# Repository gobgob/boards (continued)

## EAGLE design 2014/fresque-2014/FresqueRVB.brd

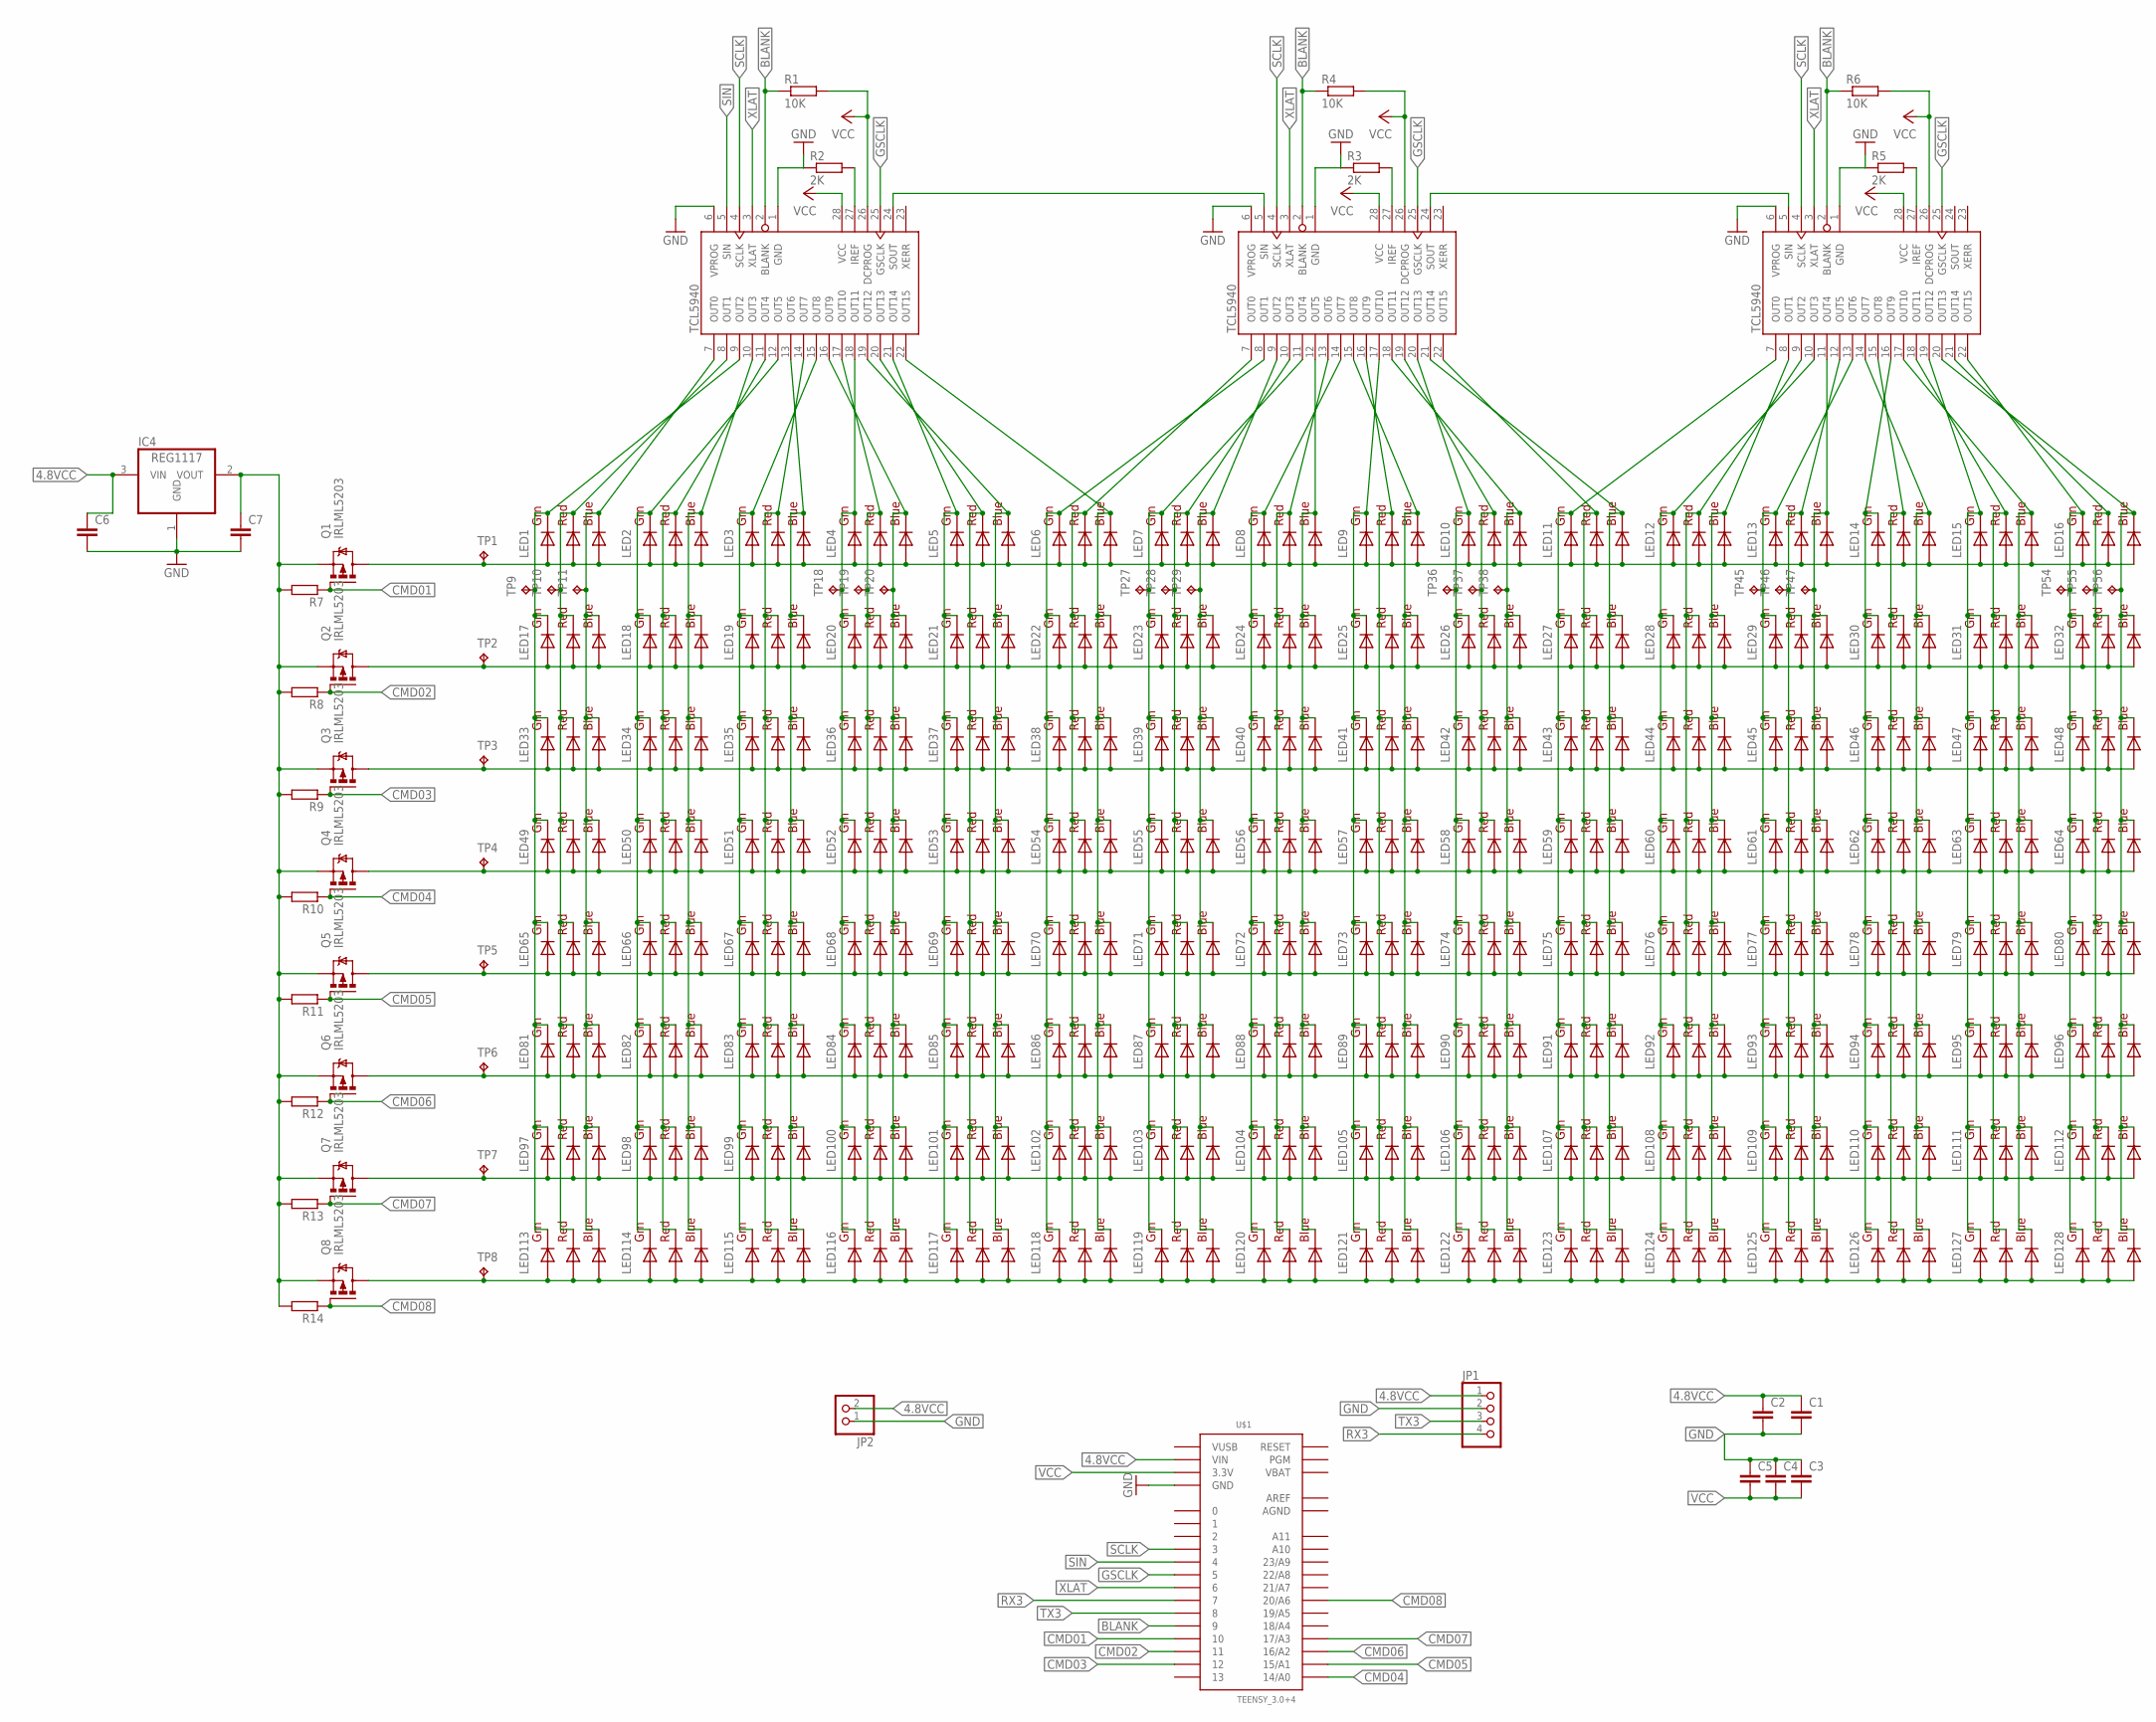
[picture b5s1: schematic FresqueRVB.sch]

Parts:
C1, C2, C3, C4, C5, C6, C7: C-EUC0603K; C0603K
IC1, IC2, IC3: TCL5940_TCL5940PWP; TCL5940_PWP
IC4: REG1117; SOT223
JP1: PINHD-1X4; 1X04
JP2: PINHD-1X2; 1X02
LED1, LED2, LED3, LED4, LED5, LED6, LED7, LED8, LED9, LED10, LED11, LED12, LED13, LED14, LED15, LED16, LED17, LED18, LED19, LED20, LED21, LED22, LED23, LED24, LED25, LED26, LED27, LED28, LED29, LED30, LED31, LED32, LED33, LED34, LED35, LED36, LED37, LED38, LED39, LED40, LED41, LED42, LED43, LED44, LED45, LED46, LED47, LED48, LED49, LED50, LED51, LED52, LED53, LED54, LED55, LED56, LED57, LED58, LED59, LED60, LED61, LED62, LED63, LED64, LED65, LED66, LED67, LED68, LED69, LED70, LED71, LED72, LED73, LED74, LED75, LED76, LED77, LED78, LED79, LED80, LED81, LED82, LED83, LED84, LED85, LED86, LED87, LED88, LED89, LED90, LED91, LED92, LED93, LED94, LED95, LED96, LED97, LED98, LED99, LED100, LED101, LED102, LED103, LED104, LED105, LED106, LED107, LED108, LED109, LED110, LED111, LED112, LED113, LED114, LED115, LED116, LED117, LED118, LED119, LED120, LED121, LED122, LED123, LED124, LED125, LED126, LED127, LED128: RGBLED5050
Q1, Q2, Q3, Q4, Q5, Q6, Q7, Q8: IRLML5203; MICRO3
R1, R4, R6: 10K; R0603
R2, R3, R5: 2K; R0603
R7, R8, R9, R10, R11, R12, R13, R14: R-EU_R0603; R0603
TP1, TP2, TP3, TP4, TP5, TP6, TP7, TP8, TP9, TP10, TP11, TP18, TP19, TP20, TP27, TP28, TP29, TP36, TP37, TP38, TP45, TP46, TP47, TP54, TP55, TP56: TPPAD1-13; P1-13
U$1: TEENSY_3.0+4

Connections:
4.8VCC: C1.1, C2.1, C6.1, IC4.3 (VIN), JP1.1, JP2.2, U$1.VBAT, U$1.VIN
AGND: U$1.AGND
AREF: U$1.AREF
BLANK: IC1.2 (BLANK), IC2.2 (BLANK), IC3.2 (BLANK), R1.1, R4.1, R6.1, U$1.9
CMD01: Q1.1 (G), R7.1, U$1.10
CMD02: Q2.1 (G), R8.1, U$1.11
CMD03: Q3.1 (G), R9.1, U$1.12
CMD04: Q4.1 (G), R10.1, U$1.14/A0
CMD05: Q5.1 (G), R11.1, U$1.15/A1
CMD06: Q6.1 (G), R12.1, U$1.16/A2
CMD07: Q7.1 (G), R13.1, U$1.17/A3
CMD08: Q8.1 (G), R14.1, U$1.20/A6
GND: C1.2, C2.2, C3.1, C4.1, C5.1, C6.2, C7.2, IC1.1 (GND), IC1.6 (VPROG), IC2.1 (GND), IC2.6 (VPROG), IC3.1 (GND), IC3.6 (VPROG), IC4.1 (GND), JP1.2, JP2.1, R2.1, R3.1, R5.1, U$1.GND, U$1.GND1 (GND)
GSCLK: IC1.25 (GSCLK), IC2.25 (GSCLK), IC3.25 (GSCLK), U$1.5
unnamed: IC2.27 (IREF), R3.2
unnamed: IC1.27 (IREF), R2.2
unnamed: IC3.27 (IREF), R5.2
unnamed: IC1.9 (OUT2), LED1.6 (GREEN_C), LED17.6 (GREEN_C), LED33.6 (GREEN_C), LED49.6 (GREEN_C), LED65.6 (GREEN_C), LED81.6 (GREEN_C), LED97.6 (GREEN_C), LED113.6 (GREEN_C), TP9.TP
unnamed: IC1.8 (OUT1), LED1.5 (RED_C), LED17.5 (RED_C), LED33.5 (RED_C), LED49.5 (RED_C), LED65.5 (RED_C), LED81.5 (RED_C), LED97.5 (RED_C), LED113.5 (RED_C), TP10.TP
unnamed: IC1.7 (OUT0), LED1.4 (BLUE_C), LED17.4 (BLUE_C), LED33.4 (BLUE_C), LED49.4 (BLUE_C), LED65.4 (BLUE_C), LED81.4 (BLUE_C), LED97.4 (BLUE_C), LED113.4 (BLUE_C), TP11.TP
unnamed: IC1.12 (OUT5), LED2.6 (GREEN_C), LED18.6 (GREEN_C), LED34.6 (GREEN_C), LED50.6 (GREEN_C), LED66.6 (GREEN_C), LED82.6 (GREEN_C), LED98.6 (GREEN_C), LED114.6 (GREEN_C)
unnamed: IC1.11 (OUT4), LED2.5 (RED_C), LED18.5 (RED_C), LED34.5 (RED_C), LED50.5 (RED_C), LED66.5 (RED_C), LED82.5 (RED_C), LED98.5 (RED_C), LED114.5 (RED_C)
unnamed: IC1.10 (OUT3), LED2.4 (BLUE_C), LED18.4 (BLUE_C), LED34.4 (BLUE_C), LED50.4 (BLUE_C), LED66.4 (BLUE_C), LED82.4 (BLUE_C), LED98.4 (BLUE_C), LED114.4 (BLUE_C)
unnamed: IC1.15 (OUT8), LED3.6 (GREEN_C), LED19.6 (GREEN_C), LED35.6 (GREEN_C), LED51.6 (GREEN_C), LED67.6 (GREEN_C), LED83.6 (GREEN_C), LED99.6 (GREEN_C), LED115.6 (GREEN_C)
unnamed: IC1.14 (OUT7), LED3.5 (RED_C), LED19.5 (RED_C), LED35.5 (RED_C), LED51.5 (RED_C), LED67.5 (RED_C), LED83.5 (RED_C), LED99.5 (RED_C), LED115.5 (RED_C)
unnamed: IC1.13 (OUT6), LED3.4 (BLUE_C), LED19.4 (BLUE_C), LED35.4 (BLUE_C), LED51.4 (BLUE_C), LED67.4 (BLUE_C), LED83.4 (BLUE_C), LED99.4 (BLUE_C), LED115.4 (BLUE_C)
unnamed: IC1.18 (OUT11), LED4.6 (GREEN_C), LED20.6 (GREEN_C), LED36.6 (GREEN_C), LED52.6 (GREEN_C), LED68.6 (GREEN_C), LED84.6 (GREEN_C), LED100.6 (GREEN_C), LED116.6 (GREEN_C), TP18.TP
unnamed: IC1.17 (OUT10), LED4.5 (RED_C), LED20.5 (RED_C), LED36.5 (RED_C), LED52.5 (RED_C), LED68.5 (RED_C), LED84.5 (RED_C), LED100.5 (RED_C), LED116.5 (RED_C), TP19.TP
unnamed: IC1.16 (OUT9), LED4.4 (BLUE_C), LED20.4 (BLUE_C), LED36.4 (BLUE_C), LED52.4 (BLUE_C), LED68.4 (BLUE_C), LED84.4 (BLUE_C), LED100.4 (BLUE_C), LED116.4 (BLUE_C), TP20.TP
unnamed: IC1.21 (OUT14), LED5.6 (GREEN_C), LED21.6 (GREEN_C), LED37.6 (GREEN_C), LED53.6 (GREEN_C), LED69.6 (GREEN_C), LED85.6 (GREEN_C), LED101.6 (GREEN_C), LED117.6 (GREEN_C)
unnamed: IC1.20 (OUT13), LED5.5 (RED_C), LED21.5 (RED_C), LED37.5 (RED_C), LED53.5 (RED_C), LED69.5 (RED_C), LED85.5 (RED_C), LED101.5 (RED_C), LED117.5 (RED_C)
unnamed: IC1.19 (OUT12), LED5.4 (BLUE_C), LED21.4 (BLUE_C), LED37.4 (BLUE_C), LED53.4 (BLUE_C), LED69.4 (BLUE_C), LED85.4 (BLUE_C), LED101.4 (BLUE_C), LED117.4 (BLUE_C)
unnamed: IC2.8 (OUT1), LED6.6 (GREEN_C), LED22.6 (GREEN_C), LED38.6 (GREEN_C), LED54.6 (GREEN_C), LED70.6 (GREEN_C), LED86.6 (GREEN_C), LED102.6 (GREEN_C), LED118.6 (GREEN_C)
unnamed: IC2.7 (OUT0), LED6.5 (RED_C), LED22.5 (RED_C), LED38.5 (RED_C), LED54.5 (RED_C), LED70.5 (RED_C), LED86.5 (RED_C), LED102.5 (RED_C), LED118.5 (RED_C)
unnamed: IC1.22 (OUT15), LED6.4 (BLUE_C), LED22.4 (BLUE_C), LED38.4 (BLUE_C), LED54.4 (BLUE_C), LED70.4 (BLUE_C), LED86.4 (BLUE_C), LED102.4 (BLUE_C), LED118.4 (BLUE_C)
unnamed: IC2.11 (OUT4), LED7.6 (GREEN_C), LED23.6 (GREEN_C), LED39.6 (GREEN_C), LED55.6 (GREEN_C), LED71.6 (GREEN_C), LED87.6 (GREEN_C), LED103.6 (GREEN_C), LED119.6 (GREEN_C), TP27.TP
unnamed: IC2.10 (OUT3), LED7.5 (RED_C), LED23.5 (RED_C), LED39.5 (RED_C), LED55.5 (RED_C), LED71.5 (RED_C), LED87.5 (RED_C), LED103.5 (RED_C), LED119.5 (RED_C), TP28.TP
unnamed: IC2.9 (OUT2), LED7.4 (BLUE_C), LED23.4 (BLUE_C), LED39.4 (BLUE_C), LED55.4 (BLUE_C), LED71.4 (BLUE_C), LED87.4 (BLUE_C), LED103.4 (BLUE_C), LED119.4 (BLUE_C), TP29.TP
unnamed: IC2.14 (OUT7), LED8.6 (GREEN_C), LED24.6 (GREEN_C), LED40.6 (GREEN_C), LED56.6 (GREEN_C), LED72.6 (GREEN_C), LED88.6 (GREEN_C), LED104.6 (GREEN_C), LED120.6 (GREEN_C)
unnamed: IC2.13 (OUT6), LED8.5 (RED_C), LED24.5 (RED_C), LED40.5 (RED_C), LED56.5 (RED_C), LED72.5 (RED_C), LED88.5 (RED_C), LED104.5 (RED_C), LED120.5 (RED_C)
unnamed: IC2.12 (OUT5), LED8.4 (BLUE_C), LED24.4 (BLUE_C), LED40.4 (BLUE_C), LED56.4 (BLUE_C), LED72.4 (BLUE_C), LED88.4 (BLUE_C), LED104.4 (BLUE_C), LED120.4 (BLUE_C)
unnamed: IC2.17 (OUT10), LED9.6 (GREEN_C), LED25.6 (GREEN_C), LED41.6 (GREEN_C), LED57.6 (GREEN_C), LED73.6 (GREEN_C), LED89.6 (GREEN_C), LED105.6 (GREEN_C), LED121.6 (GREEN_C)
unnamed: IC2.16 (OUT9), LED9.5 (RED_C), LED25.5 (RED_C), LED41.5 (RED_C), LED57.5 (RED_C), LED73.5 (RED_C), LED89.5 (RED_C), LED105.5 (RED_C), LED121.5 (RED_C)
unnamed: IC2.15 (OUT8), LED9.4 (BLUE_C), LED25.4 (BLUE_C), LED41.4 (BLUE_C), LED57.4 (BLUE_C), LED73.4 (BLUE_C), LED89.4 (BLUE_C), LED105.4 (BLUE_C), LED121.4 (BLUE_C)
unnamed: IC2.20 (OUT13), LED10.6 (GREEN_C), LED26.6 (GREEN_C), LED42.6 (GREEN_C), LED58.6 (GREEN_C), LED74.6 (GREEN_C), LED90.6 (GREEN_C), LED106.6 (GREEN_C), LED122.6 (GREEN_C), TP36.TP
unnamed: IC2.19 (OUT12), LED10.5 (RED_C), LED26.5 (RED_C), LED42.5 (RED_C), LED58.5 (RED_C), LED74.5 (RED_C), LED90.5 (RED_C), LED106.5 (RED_C), LED122.5 (RED_C), TP37.TP
unnamed: IC2.18 (OUT11), LED10.4 (BLUE_C), LED26.4 (BLUE_C), LED42.4 (BLUE_C), LED58.4 (BLUE_C), LED74.4 (BLUE_C), LED90.4 (BLUE_C), LED106.4 (BLUE_C), LED122.4 (BLUE_C), TP38.TP
unnamed: IC3.7 (OUT0), LED11.6 (GREEN_C), LED27.6 (GREEN_C), LED43.6 (GREEN_C), LED59.6 (GREEN_C), LED75.6 (GREEN_C), LED91.6 (GREEN_C), LED107.6 (GREEN_C), LED123.6 (GREEN_C)
unnamed: IC2.22 (OUT15), LED11.5 (RED_C), LED27.5 (RED_C), LED43.5 (RED_C), LED59.5 (RED_C), LED75.5 (RED_C), LED91.5 (RED_C), LED107.5 (RED_C), LED123.5 (RED_C)
unnamed: IC2.21 (OUT14), LED11.4 (BLUE_C), LED27.4 (BLUE_C), LED43.4 (BLUE_C), LED59.4 (BLUE_C), LED75.4 (BLUE_C), LED91.4 (BLUE_C), LED107.4 (BLUE_C), LED123.4 (BLUE_C)
unnamed: IC3.10 (OUT3), LED12.6 (GREEN_C), LED28.6 (GREEN_C), LED44.6 (GREEN_C), LED60.6 (GREEN_C), LED76.6 (GREEN_C), LED92.6 (GREEN_C), LED108.6 (GREEN_C), LED124.6 (GREEN_C)
unnamed: IC3.9 (OUT2), LED12.5 (RED_C), LED28.5 (RED_C), LED44.5 (RED_C), LED60.5 (RED_C), LED76.5 (RED_C), LED92.5 (RED_C), LED108.5 (RED_C), LED124.5 (RED_C)
unnamed: IC3.8 (OUT1), LED12.4 (BLUE_C), LED28.4 (BLUE_C), LED44.4 (BLUE_C), LED60.4 (BLUE_C), LED76.4 (BLUE_C), LED92.4 (BLUE_C), LED108.4 (BLUE_C), LED124.4 (BLUE_C)
unnamed: IC3.13 (OUT6), LED13.6 (GREEN_C), LED29.6 (GREEN_C), LED45.6 (GREEN_C), LED61.6 (GREEN_C), LED77.6 (GREEN_C), LED93.6 (GREEN_C), LED109.6 (GREEN_C), LED125.6 (GREEN_C), TP45.TP
unnamed: IC3.12 (OUT5), LED13.5 (RED_C), LED29.5 (RED_C), LED45.5 (RED_C), LED61.5 (RED_C), LED77.5 (RED_C), LED93.5 (RED_C), LED109.5 (RED_C), LED125.5 (RED_C), TP46.TP
unnamed: IC3.11 (OUT4), LED13.4 (BLUE_C), LED29.4 (BLUE_C), LED45.4 (BLUE_C), LED61.4 (BLUE_C), LED77.4 (BLUE_C), LED93.4 (BLUE_C), LED109.4 (BLUE_C), LED125.4 (BLUE_C), TP47.TP
unnamed: IC3.16 (OUT9), LED14.6 (GREEN_C), LED30.6 (GREEN_C), LED46.6 (GREEN_C), LED62.6 (GREEN_C), LED78.6 (GREEN_C), LED94.6 (GREEN_C), LED110.6 (GREEN_C), LED126.6 (GREEN_C)
unnamed: IC3.15 (OUT8), LED14.5 (RED_C), LED30.5 (RED_C), LED46.5 (RED_C), LED62.5 (RED_C), LED78.5 (RED_C), LED94.5 (RED_C), LED110.5 (RED_C), LED126.5 (RED_C)
unnamed: IC3.14 (OUT7), LED14.4 (BLUE_C), LED30.4 (BLUE_C), LED46.4 (BLUE_C), LED62.4 (BLUE_C), LED78.4 (BLUE_C), LED94.4 (BLUE_C), LED110.4 (BLUE_C), LED126.4 (BLUE_C)
unnamed: IC3.19 (OUT12), LED15.6 (GREEN_C), LED31.6 (GREEN_C), LED47.6 (GREEN_C), LED63.6 (GREEN_C), LED79.6 (GREEN_C), LED95.6 (GREEN_C), LED111.6 (GREEN_C), LED127.6 (GREEN_C)
unnamed: IC3.18 (OUT11), LED15.5 (RED_C), LED31.5 (RED_C), LED47.5 (RED_C), LED63.5 (RED_C), LED79.5 (RED_C), LED95.5 (RED_C), LED111.5 (RED_C), LED127.5 (RED_C)
unnamed: IC3.17 (OUT10), LED15.4 (BLUE_C), LED31.4 (BLUE_C), LED47.4 (BLUE_C), LED63.4 (BLUE_C), LED79.4 (BLUE_C), LED95.4 (BLUE_C), LED111.4 (BLUE_C), LED127.4 (BLUE_C)
unnamed: IC3.22 (OUT15), LED16.6 (GREEN_C), LED32.6 (GREEN_C), LED48.6 (GREEN_C), LED64.6 (GREEN_C), LED80.6 (GREEN_C), LED96.6 (GREEN_C), LED112.6 (GREEN_C), LED128.6 (GREEN_C), TP54.TP
unnamed: IC3.21 (OUT14), LED16.5 (RED_C), LED32.5 (RED_C), LED48.5 (RED_C), LED64.5 (RED_C), LED80.5 (RED_C), LED96.5 (RED_C), LED112.5 (RED_C), LED128.5 (RED_C), TP55.TP
unnamed: IC3.20 (OUT13), LED16.4 (BLUE_C), LED32.4 (BLUE_C), LED48.4 (BLUE_C), LED64.4 (BLUE_C), LED80.4 (BLUE_C), LED96.4 (BLUE_C), LED112.4 (BLUE_C), LED128.4 (BLUE_C), TP56.TP
unnamed: IC1.24 (SOUT), IC2.5 (SIN)
unnamed: IC2.24 (SOUT), IC3.5 (SIN)
unnamed: LED1.1 (GREEN_A), LED1.2 (RED_A), LED1.3 (BLUE_A), LED2.1 (GREEN_A), LED2.2 (RED_A), LED2.3 (BLUE_A), LED3.1 (GREEN_A), LED3.2 (RED_A), LED3.3 (BLUE_A), LED4.1 (GREEN_A), LED4.2 (RED_A), LED4.3 (BLUE_A), LED5.1 (GREEN_A), LED5.2 (RED_A), LED5.3 (BLUE_A), LED6.1 (GREEN_A), LED6.2 (RED_A), LED6.3 (BLUE_A), LED7.1 (GREEN_A), LED7.2 (RED_A), LED7.3 (BLUE_A), LED8.1 (GREEN_A), LED8.2 (RED_A), LED8.3 (BLUE_A), LED9.1 (GREEN_A), LED9.2 (RED_A), LED9.3 (BLUE_A), LED10.1 (GREEN_A), LED10.2 (RED_A), LED10.3 (BLUE_A), LED11.1 (GREEN_A), LED11.2 (RED_A), LED11.3 (BLUE_A), LED12.1 (GREEN_A), LED12.2 (RED_A), LED12.3 (BLUE_A), LED13.1 (GREEN_A), LED13.2 (RED_A), LED13.3 (BLUE_A), LED14.1 (GREEN_A), LED14.2 (RED_A), LED14.3 (BLUE_A), LED15.1 (GREEN_A), LED15.2 (RED_A), LED15.3 (BLUE_A), LED16.1 (GREEN_A), LED16.2 (RED_A), LED16.3 (BLUE_A), Q1.3 (D), TP1.TP
unnamed: LED17.1 (GREEN_A), LED17.2 (RED_A), LED17.3 (BLUE_A), LED18.1 (GREEN_A), LED18.2 (RED_A), LED18.3 (BLUE_A), LED19.1 (GREEN_A), LED19.2 (RED_A), LED19.3 (BLUE_A), LED20.1 (GREEN_A), LED20.2 (RED_A), LED20.3 (BLUE_A), LED21.1 (GREEN_A), LED21.2 (RED_A), LED21.3 (BLUE_A), LED22.1 (GREEN_A), LED22.2 (RED_A), LED22.3 (BLUE_A), LED23.1 (GREEN_A), LED23.2 (RED_A), LED23.3 (BLUE_A), LED24.1 (GREEN_A), LED24.2 (RED_A), LED24.3 (BLUE_A), LED25.1 (GREEN_A), LED25.2 (RED_A), LED25.3 (BLUE_A), LED26.1 (GREEN_A), LED26.2 (RED_A), LED26.3 (BLUE_A), LED27.1 (GREEN_A), LED27.2 (RED_A), LED27.3 (BLUE_A), LED28.1 (GREEN_A), LED28.2 (RED_A), LED28.3 (BLUE_A), LED29.1 (GREEN_A), LED29.2 (RED_A), LED29.3 (BLUE_A), LED30.1 (GREEN_A), LED30.2 (RED_A), LED30.3 (BLUE_A), LED31.1 (GREEN_A), LED31.2 (RED_A), LED31.3 (BLUE_A), LED32.1 (GREEN_A), LED32.2 (RED_A), LED32.3 (BLUE_A), Q2.3 (D), TP2.TP
unnamed: C7.1, IC4.2 (VOUT), Q1.2 (S), Q2.2 (S), Q3.2 (S), Q4.2 (S), Q5.2 (S), Q6.2 (S), Q7.2 (S), Q8.2 (S), R7.2, R8.2, R9.2, R10.2, R11.2, R12.2, R13.2, R14.2
unnamed: LED33.1 (GREEN_A), LED33.2 (RED_A), LED33.3 (BLUE_A), LED34.1 (GREEN_A), LED34.2 (RED_A), LED34.3 (BLUE_A), LED35.1 (GREEN_A), LED35.2 (RED_A), LED35.3 (BLUE_A), LED36.1 (GREEN_A), LED36.2 (RED_A), LED36.3 (BLUE_A), LED37.1 (GREEN_A), LED37.2 (RED_A), LED37.3 (BLUE_A), LED38.1 (GREEN_A), LED38.2 (RED_A), LED38.3 (BLUE_A), LED39.1 (GREEN_A), LED39.2 (RED_A), LED39.3 (BLUE_A), LED40.1 (GREEN_A), LED40.2 (RED_A), LED40.3 (BLUE_A), LED41.1 (GREEN_A), LED41.2 (RED_A), LED41.3 (BLUE_A), LED42.1 (GREEN_A), LED42.2 (RED_A), LED42.3 (BLUE_A), LED43.1 (GREEN_A), LED43.2 (RED_A), LED43.3 (BLUE_A), LED44.1 (GREEN_A), LED44.2 (RED_A), LED44.3 (BLUE_A), LED45.1 (GREEN_A), LED45.2 (RED_A), LED45.3 (BLUE_A), LED46.1 (GREEN_A), LED46.2 (RED_A), LED46.3 (BLUE_A), LED47.1 (GREEN_A), LED47.2 (RED_A), LED47.3 (BLUE_A), LED48.1 (GREEN_A), LED48.2 (RED_A), LED48.3 (BLUE_A), Q3.3 (D), TP3.TP
unnamed: LED49.1 (GREEN_A), LED49.2 (RED_A), LED49.3 (BLUE_A), LED50.1 (GREEN_A), LED50.2 (RED_A), LED50.3 (BLUE_A), LED51.1 (GREEN_A), LED51.2 (RED_A), LED51.3 (BLUE_A), LED52.1 (GREEN_A), LED52.2 (RED_A), LED52.3 (BLUE_A), LED53.1 (GREEN_A), LED53.2 (RED_A), LED53.3 (BLUE_A), LED54.1 (GREEN_A), LED54.2 (RED_A), LED54.3 (BLUE_A), LED55.1 (GREEN_A), LED55.2 (RED_A), LED55.3 (BLUE_A), LED56.1 (GREEN_A), LED56.2 (RED_A), LED56.3 (BLUE_A), LED57.1 (GREEN_A), LED57.2 (RED_A), LED57.3 (BLUE_A), LED58.1 (GREEN_A), LED58.2 (RED_A), LED58.3 (BLUE_A), LED59.1 (GREEN_A), LED59.2 (RED_A), LED59.3 (BLUE_A), LED60.1 (GREEN_A), LED60.2 (RED_A), LED60.3 (BLUE_A), LED61.1 (GREEN_A), LED61.2 (RED_A), LED61.3 (BLUE_A), LED62.1 (GREEN_A), LED62.2 (RED_A), LED62.3 (BLUE_A), LED63.1 (GREEN_A), LED63.2 (RED_A), LED63.3 (BLUE_A), LED64.1 (GREEN_A), LED64.2 (RED_A), LED64.3 (BLUE_A), Q4.3 (D), TP4.TP
unnamed: LED65.1 (GREEN_A), LED65.2 (RED_A), LED65.3 (BLUE_A), LED66.1 (GREEN_A), LED66.2 (RED_A), LED66.3 (BLUE_A), LED67.1 (GREEN_A), LED67.2 (RED_A), LED67.3 (BLUE_A), LED68.1 (GREEN_A), LED68.2 (RED_A), LED68.3 (BLUE_A), LED69.1 (GREEN_A), LED69.2 (RED_A), LED69.3 (BLUE_A), LED70.1 (GREEN_A), LED70.2 (RED_A), LED70.3 (BLUE_A), LED71.1 (GREEN_A), LED71.2 (RED_A), LED71.3 (BLUE_A), LED72.1 (GREEN_A), LED72.2 (RED_A), LED72.3 (BLUE_A), LED73.1 (GREEN_A), LED73.2 (RED_A), LED73.3 (BLUE_A), LED74.1 (GREEN_A), LED74.2 (RED_A), LED74.3 (BLUE_A), LED75.1 (GREEN_A), LED75.2 (RED_A), LED75.3 (BLUE_A), LED76.1 (GREEN_A), LED76.2 (RED_A), LED76.3 (BLUE_A), LED77.1 (GREEN_A), LED77.2 (RED_A), LED77.3 (BLUE_A), LED78.1 (GREEN_A), LED78.2 (RED_A), LED78.3 (BLUE_A), LED79.1 (GREEN_A), LED79.2 (RED_A), LED79.3 (BLUE_A), LED80.1 (GREEN_A), LED80.2 (RED_A), LED80.3 (BLUE_A), Q5.3 (D), TP5.TP
unnamed: LED81.1 (GREEN_A), LED81.2 (RED_A), LED81.3 (BLUE_A), LED82.1 (GREEN_A), LED82.2 (RED_A), LED82.3 (BLUE_A), LED83.1 (GREEN_A), LED83.2 (RED_A), LED83.3 (BLUE_A), LED84.1 (GREEN_A), LED84.2 (RED_A), LED84.3 (BLUE_A), LED85.1 (GREEN_A), LED85.2 (RED_A), LED85.3 (BLUE_A), LED86.1 (GREEN_A), LED86.2 (RED_A), LED86.3 (BLUE_A), LED87.1 (GREEN_A), LED87.2 (RED_A), LED87.3 (BLUE_A), LED88.1 (GREEN_A), LED88.2 (RED_A), LED88.3 (BLUE_A), LED89.1 (GREEN_A), LED89.2 (RED_A), LED89.3 (BLUE_A), LED90.1 (GREEN_A), LED90.2 (RED_A), LED90.3 (BLUE_A), LED91.1 (GREEN_A), LED91.2 (RED_A), LED91.3 (BLUE_A), LED92.1 (GREEN_A), LED92.2 (RED_A), LED92.3 (BLUE_A), LED93.1 (GREEN_A), LED93.2 (RED_A), LED93.3 (BLUE_A), LED94.1 (GREEN_A), LED94.2 (RED_A), LED94.3 (BLUE_A), LED95.1 (GREEN_A), LED95.2 (RED_A), LED95.3 (BLUE_A), LED96.1 (GREEN_A), LED96.2 (RED_A), LED96.3 (BLUE_A), Q6.3 (D), TP6.TP
unnamed: LED97.1 (GREEN_A), LED97.2 (RED_A), LED97.3 (BLUE_A), LED98.1 (GREEN_A), LED98.2 (RED_A), LED98.3 (BLUE_A), LED99.1 (GREEN_A), LED99.2 (RED_A), LED99.3 (BLUE_A), LED100.1 (GREEN_A), LED100.2 (RED_A), LED100.3 (BLUE_A), LED101.1 (GREEN_A), LED101.2 (RED_A), LED101.3 (BLUE_A), LED102.1 (GREEN_A), LED102.2 (RED_A), LED102.3 (BLUE_A), LED103.1 (GREEN_A), LED103.2 (RED_A), LED103.3 (BLUE_A), LED104.1 (GREEN_A), LED104.2 (RED_A), LED104.3 (BLUE_A), LED105.1 (GREEN_A), LED105.2 (RED_A), LED105.3 (BLUE_A), LED106.1 (GREEN_A), LED106.2 (RED_A), LED106.3 (BLUE_A), LED107.1 (GREEN_A), LED107.2 (RED_A), LED107.3 (BLUE_A), LED108.1 (GREEN_A), LED108.2 (RED_A), LED108.3 (BLUE_A), LED109.1 (GREEN_A), LED109.2 (RED_A), LED109.3 (BLUE_A), LED110.1 (GREEN_A), LED110.2 (RED_A), LED110.3 (BLUE_A), LED111.1 (GREEN_A), LED111.2 (RED_A), LED111.3 (BLUE_A), LED112.1 (GREEN_A), LED112.2 (RED_A), LED112.3 (BLUE_A), Q7.3 (D), TP7.TP
unnamed: LED113.1 (GREEN_A), LED113.2 (RED_A), LED113.3 (BLUE_A), LED114.1 (GREEN_A), LED114.2 (RED_A), LED114.3 (BLUE_A), LED115.1 (GREEN_A), LED115.2 (RED_A), LED115.3 (BLUE_A), LED116.1 (GREEN_A), LED116.2 (RED_A), LED116.3 (BLUE_A), LED117.1 (GREEN_A), LED117.2 (RED_A), LED117.3 (BLUE_A), LED118.1 (GREEN_A), LED118.2 (RED_A), LED118.3 (BLUE_A), LED119.1 (GREEN_A), LED119.2 (RED_A), LED119.3 (BLUE_A), LED120.1 (GREEN_A), LED120.2 (RED_A), LED120.3 (BLUE_A), LED121.1 (GREEN_A), LED121.2 (RED_A), LED121.3 (BLUE_A), LED122.1 (GREEN_A), LED122.2 (RED_A), LED122.3 (BLUE_A), LED123.1 (GREEN_A), LED123.2 (RED_A), LED123.3 (BLUE_A), LED124.1 (GREEN_A), LED124.2 (RED_A), LED124.3 (BLUE_A), LED125.1 (GREEN_A), LED125.2 (RED_A), LED125.3 (BLUE_A), LED126.1 (GREEN_A), LED126.2 (RED_A), LED126.3 (BLUE_A), LED127.1 (GREEN_A), LED127.2 (RED_A), LED127.3 (BLUE_A), LED128.1 (GREEN_A), LED128.2 (RED_A), LED128.3 (BLUE_A), Q8.3 (D), TP8.TP
RX3: JP1.4, U$1.7
SCLK: IC1.4 (SCLK), IC2.4 (SCLK), IC3.4 (SCLK), U$1.3
SIN: IC1.5 (SIN), U$1.4
TX3: JP1.3, U$1.8
VCC: C3.2, C4.2, C5.2, IC1.26 (DCPROG), IC1.28 (VCC), IC2.26 (DCPROG), IC2.28 (VCC), IC3.26 (DCPROG), IC3.28 (VCC), R1.2, R4.2, R6.2, U$1.3.3V, U$1.3.3V1 (3.3V)
VUSB: U$1.VUSB
XLAT: IC1.3 (XLAT), IC2.3 (XLAT), IC3.3 (XLAT), U$1.6

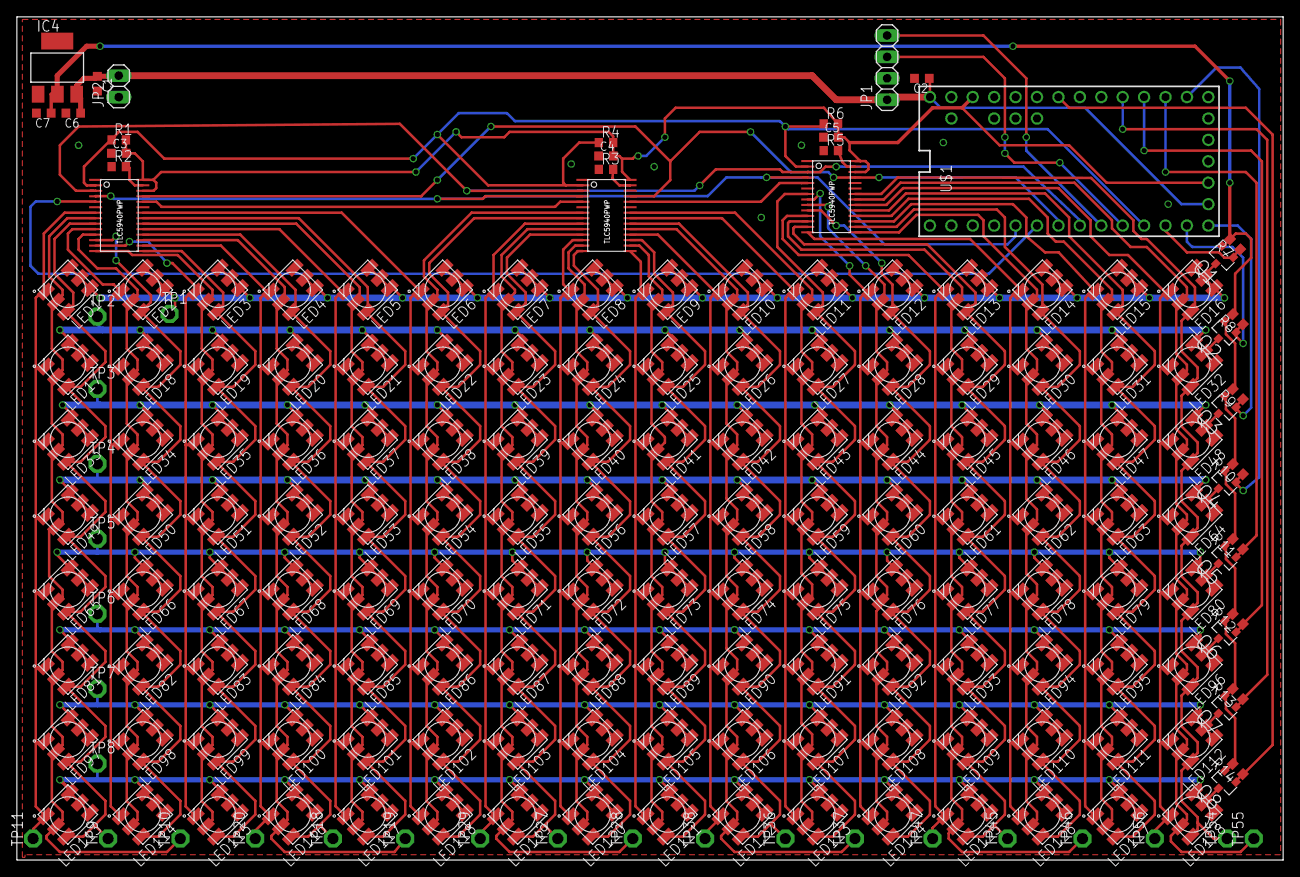
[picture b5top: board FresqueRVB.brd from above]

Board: 2 copper layers, 150.2 x 100.0 mm, 190 parts (0 on the bottom side), 80 nets.

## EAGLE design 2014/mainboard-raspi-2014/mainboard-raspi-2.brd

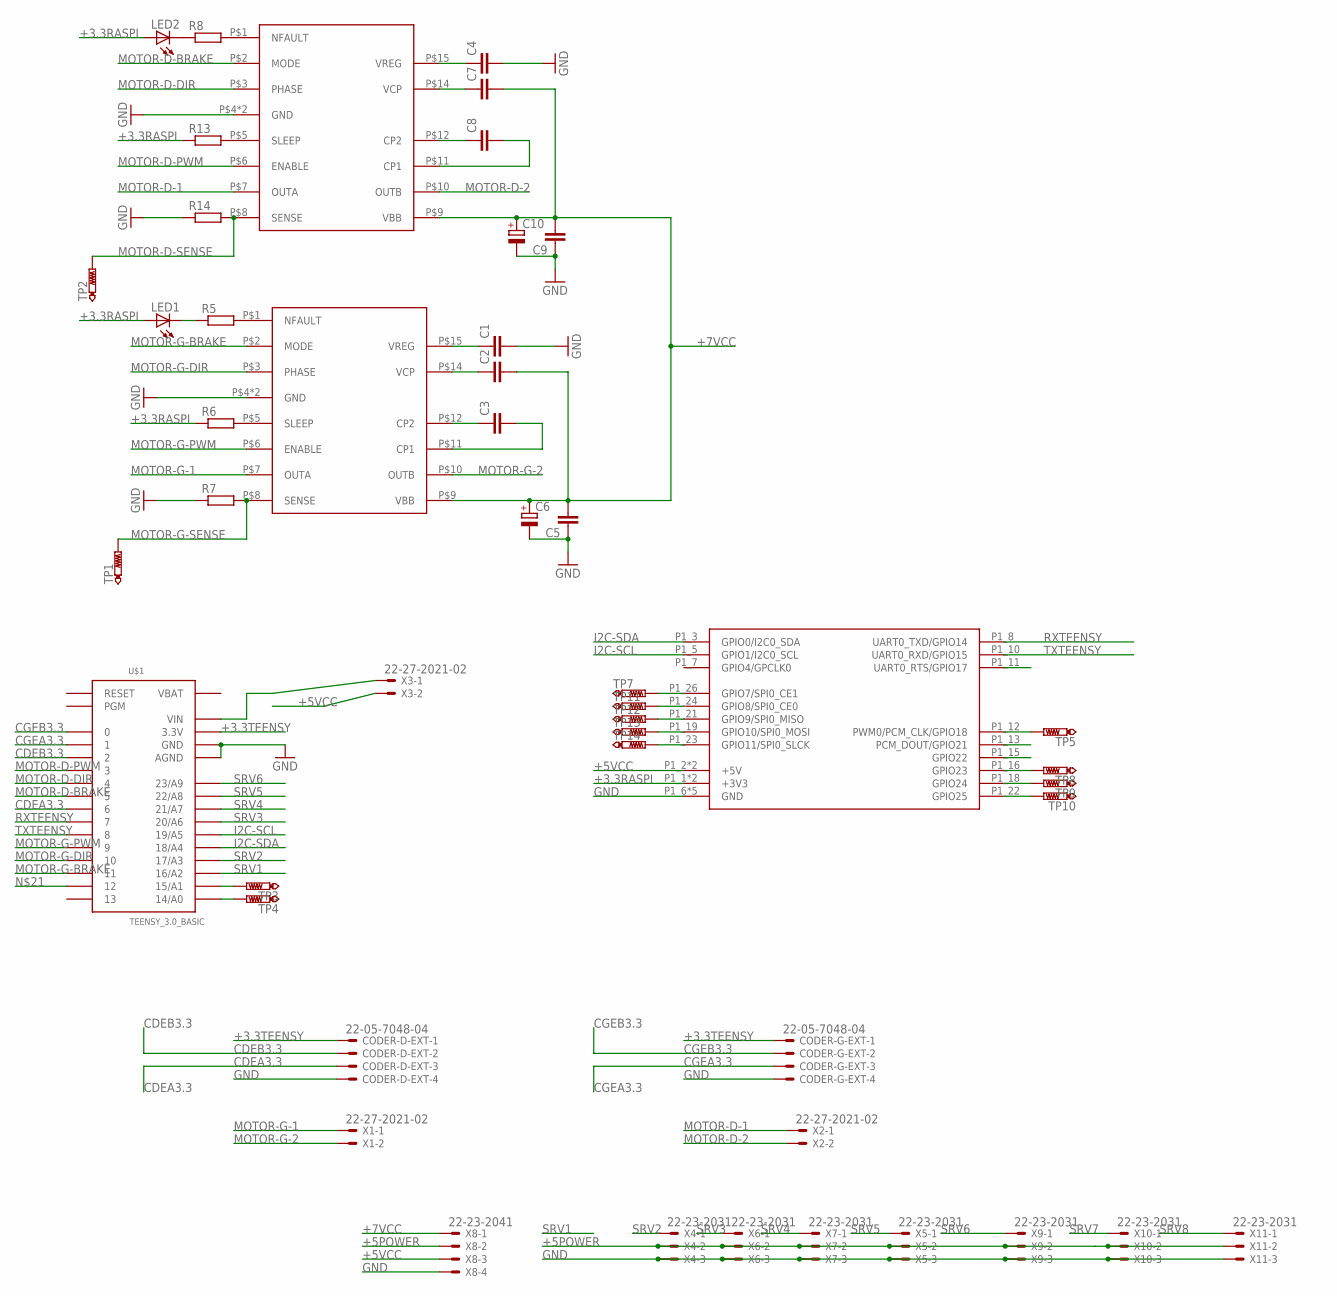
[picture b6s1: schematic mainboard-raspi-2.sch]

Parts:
C1, C2, C3, C4, C5, C7, C8, C9: C-EUC0805K; C0805K
C6, C10: CPOL-EUE3.5-8; E3,5-8
CODER-D-EXT: 22-05-7048-04; 7395-04
CODER-G-EXT: 22-05-7048-04; 7395-04
LED1, LED2: LED3MM
R5, R7, R8, R14: R-EU_R0805W; R0805W
R6, R13: R-EU_0204/7; 0204/7
TP1, TP2, TP3, TP4, TP5, TP7, TP8, TP9, TP10, TP11, TP12, TP13, TP14: PTR1PAD1-13; P1-13
U$1: TEENSY_3.0_BASIC
U$3, U$4: A3950-DIL; DIL16
U$5: RPI-B-V1SHIELD; RPI-B-V1-SHIELD
X1, X2, X3: 22-27-2021-02; 6410-02
X4, X5, X6, X7, X9, X10, X11: 22-23-2031
X8: 22-23-2041

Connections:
+3.3RASPI: LED1.A, LED2.A, R6.1, R13.1, U$5.P1_1 (+3V3), U$5.P1_17 (+3V3)
+3.3TEENSY: CODER-D-EXT.1, CODER-G-EXT.1, U$1.3.3V, U$1.3.3V1 (3.3V)
+5POWER: X4.2, X5.2, X6.2, X7.2, X8.2, X9.2, X10.2, X11.2
+5VCC: U$5.P1_2 (+5V), U$5.P1_4 (+5V), X3.2, X8.3
+7VCC: C2.2, C5.2, C6.+, C7.2, C9.2, C10.+, U$3.P$9 (VBB), U$4.P$9 (VBB), X8.1
CDEA3.3: CODER-D-EXT.3, U$1.6
CDEB3.3: CODER-D-EXT.2, U$1.2
CGEA3.3: CODER-G-EXT.3, U$1.1
CGEB3.3: CODER-G-EXT.2, U$1.0
GND: C1.2, C4.2, C5.1, C6.-, C9.1, C10.-, CODER-D-EXT.4, CODER-G-EXT.4, R7.1, R14.1, U$1.AGND, U$1.GND, U$1.GND1 (GND), U$3.P$4 (GND), U$3.P$13 (GND), U$4.P$4 (GND), U$4.P$13 (GND), U$5.P1_6 (GND), U$5.P1_9 (GND), U$5.P1_14 (GND), U$5.P1_20 (GND), U$5.P1_25 (GND), X4.3, X5.3, X6.3, X7.3, X8.4, X9.3, X10.3, X11.3
I2C-SCL: U$1.19/A5, U$5.P1_5 (GPIO1/I2C0_SCL)
I2C-SDA: U$1.18/A4, U$5.P1_3 (GPIO0/I2C0_SDA)
MOTOR-D-1: U$4.P$7 (OUTA), X2.1
MOTOR-D-2: U$4.P$10 (OUTB), X2.2
MOTOR-D-BRAKE: U$1.5, U$4.P$2 (MODE)
MOTOR-D-DIR: U$1.4, U$4.P$3 (PHASE)
MOTOR-D-PWM: U$1.3, U$4.P$6 (ENABLE)
MOTOR-D-SENSE: R14.2, TP2.TP, U$4.P$8 (SENSE)
MOTOR-G-1: U$3.P$7 (OUTA), X1.1
MOTOR-G-2: U$3.P$10 (OUTB), X1.2
MOTOR-G-BRAKE: U$1.11, U$3.P$2 (MODE)
MOTOR-G-DIR: U$1.10, U$3.P$3 (PHASE)
MOTOR-G-PWM: U$1.9, U$3.P$6 (ENABLE)
MOTOR-G-SENSE: R7.2, TP1.TP, U$3.P$8 (SENSE)
unnamed: TP3.TP, U$1.15/A1
unnamed: U$1.VIN, X3.1
unnamed: TP4.TP, U$1.14/A0
unnamed: R5.2, U$3.P$1 (NFAULT)
unnamed: R6.2, U$3.P$5 (SLEEP)
unnamed: R8.2, U$4.P$1 (NFAULT)
unnamed: C1.1, U$3.P$15 (VREG)
unnamed: C2.1, U$3.P$14 (VCP)
unnamed: C3.1, U$3.P$12 (CP2)
unnamed: LED1.K (C), R5.1
unnamed: R13.2, U$4.P$5 (SLEEP)
unnamed: C4.1, U$4.P$15 (VREG)
unnamed: C7.1, U$4.P$14 (VCP)
unnamed: C3.2, U$3.P$11 (CP1)
unnamed: C8.1, U$4.P$12 (CP2)
unnamed: TP5.TP, U$5.P1_12 (PWM0/PCM_CLK/GPIO18)
unnamed: C8.2, U$4.P$11 (CP1)
unnamed: LED2.K (C), R8.1
unnamed: TP8.TP, U$5.P1_16 (GPIO23)
unnamed: TP9.TP, U$5.P1_18 (GPIO24)
unnamed: TP10.TP, U$5.P1_22 (GPIO25)
unnamed: TP7.TP, U$5.P1_26 (GPIO7/SPI0_CE1)
unnamed: TP11.TP, U$5.P1_24 (GPIO8/SPI0_CE0)
unnamed: TP12.TP, U$5.P1_21 (GPIO9/SPI0_MISO)
unnamed: TP13.TP, U$5.P1_19 (GPIO10/SPI0_MOSI)
unnamed: TP14.TP, U$5.P1_23 (GPIO11/SPI0_SLCK)
RXTEENSY: U$1.7, U$5.P1_8 (UART0_TXD/GPIO14)
SRV1: U$1.16/A2
SRV2: U$1.17/A3, X4.1
SRV3: U$1.20/A6, X6.1
SRV4: U$1.21/A7, X7.1
SRV5: U$1.22/A8, X5.1
SRV6: U$1.23/A9, X9.1
SRV7: X10.1
SRV8: X11.1
TXTEENSY: U$1.8, U$5.P1_10 (UART0_RXD/GPIO15)
VBAT: U$1.VBAT

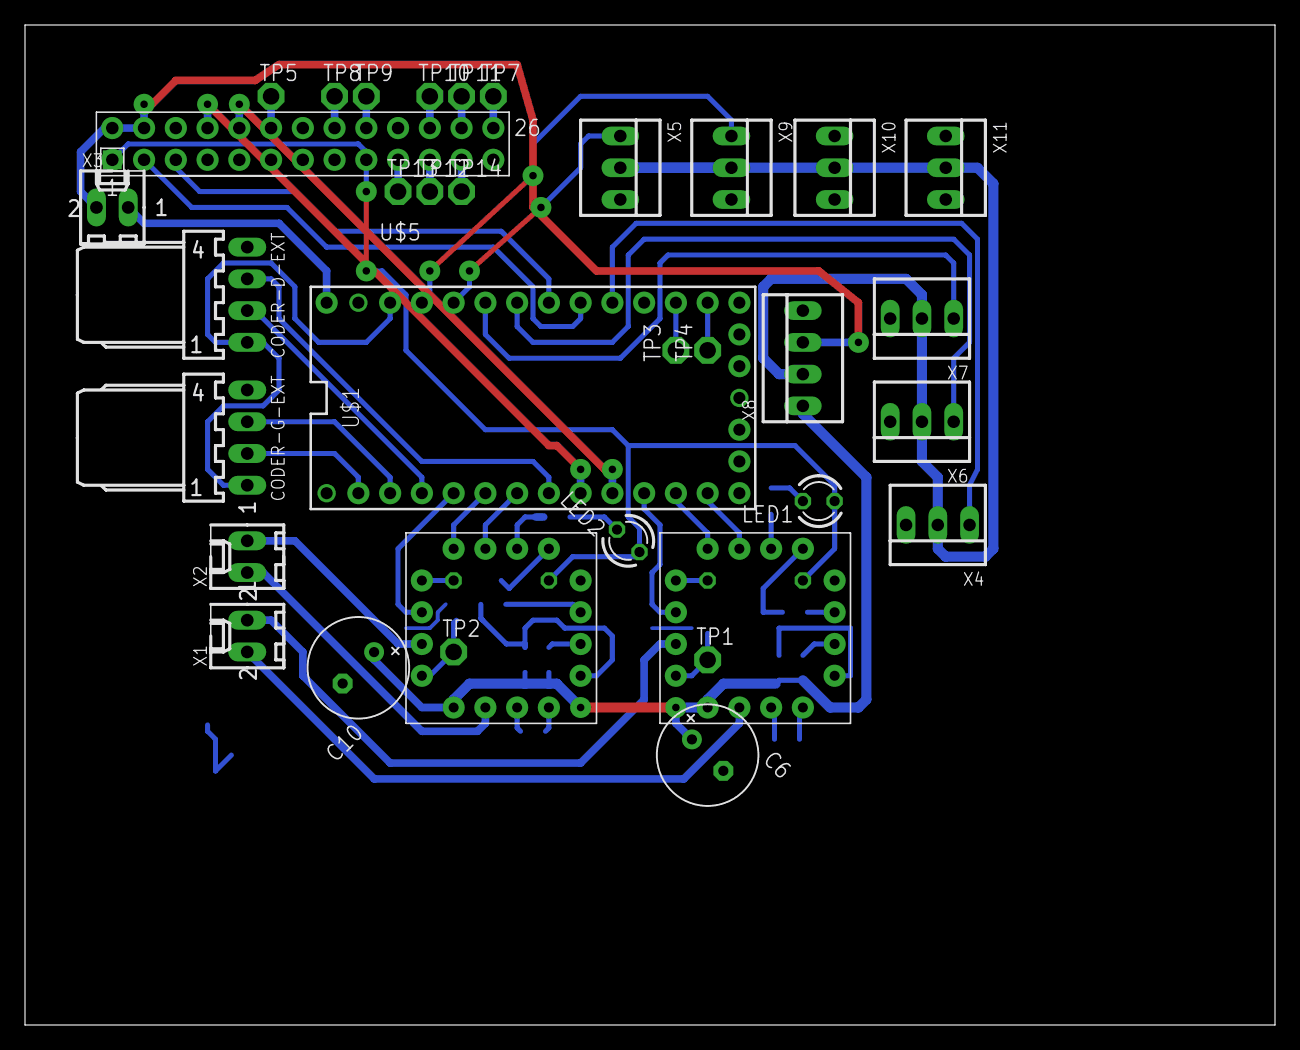
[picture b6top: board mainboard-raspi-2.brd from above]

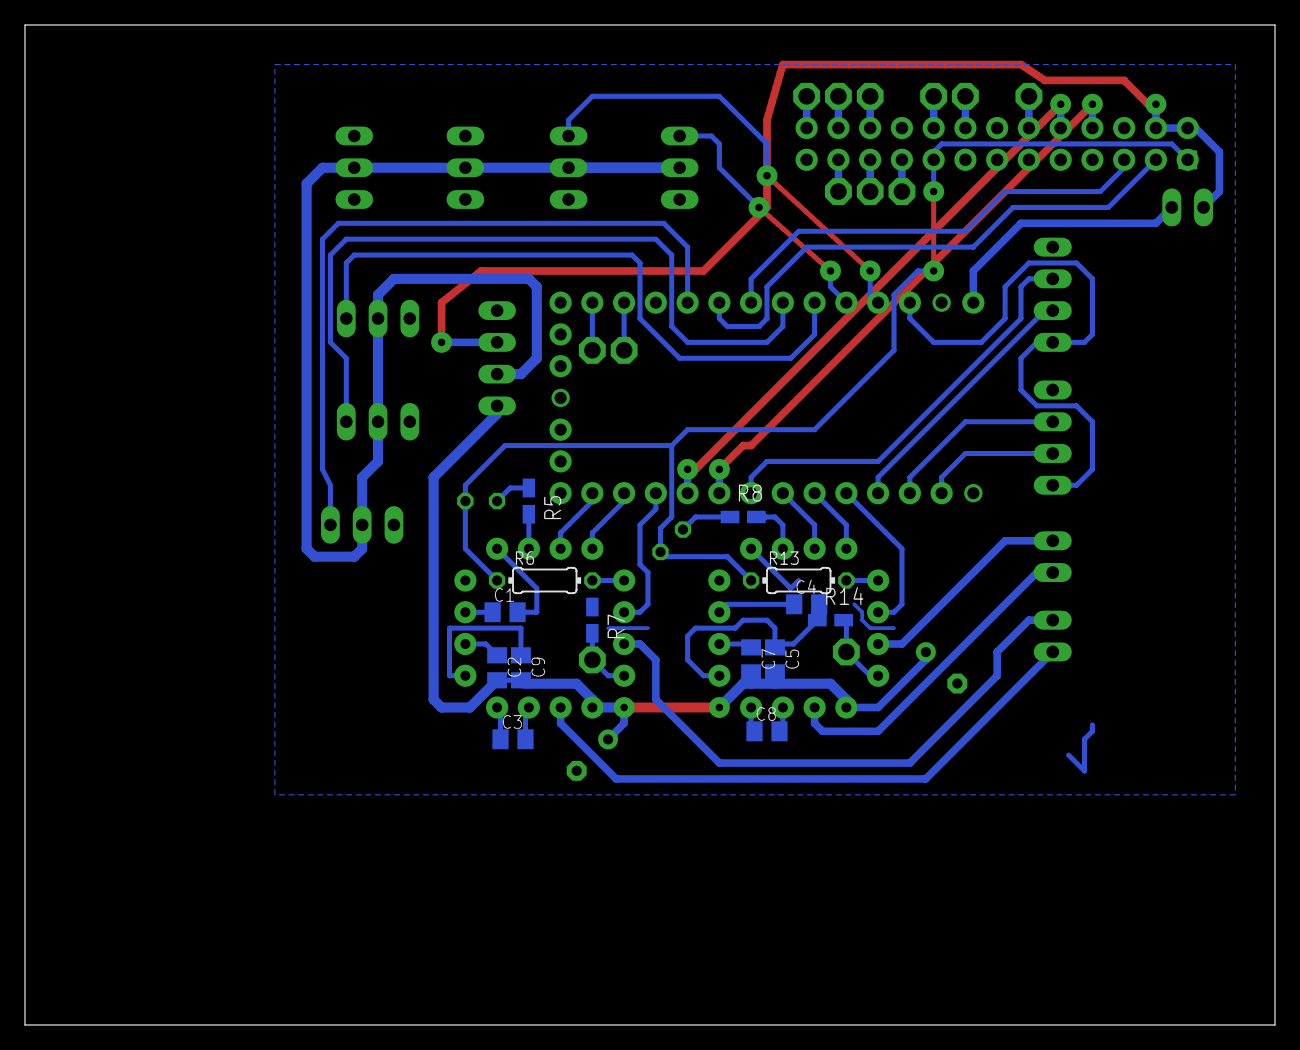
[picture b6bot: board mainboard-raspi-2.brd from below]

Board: 2 copper layers, 100.0 x 80.0 mm, 48 parts (14 on the bottom side), 57 nets.
